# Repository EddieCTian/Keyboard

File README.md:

# Keyboard

Repository for .sch, .brd, and qmk configuration files for a keyboard I tried to desgin

## Version 1

Doesn't work due to a clock frequency mismatch between VCC (3.3V) and the required voltage for that clock (5V). As a result, it cannot connect to USB and also has layout issues. 

## Version 2

Fixed problems in version 1, but has yet to be checked or sent to a manufacturer to fabricate. 

Stopped working on this project since it got prohibitively expensive to purchase parts.

Maybe in the future it will become a working keyboard.

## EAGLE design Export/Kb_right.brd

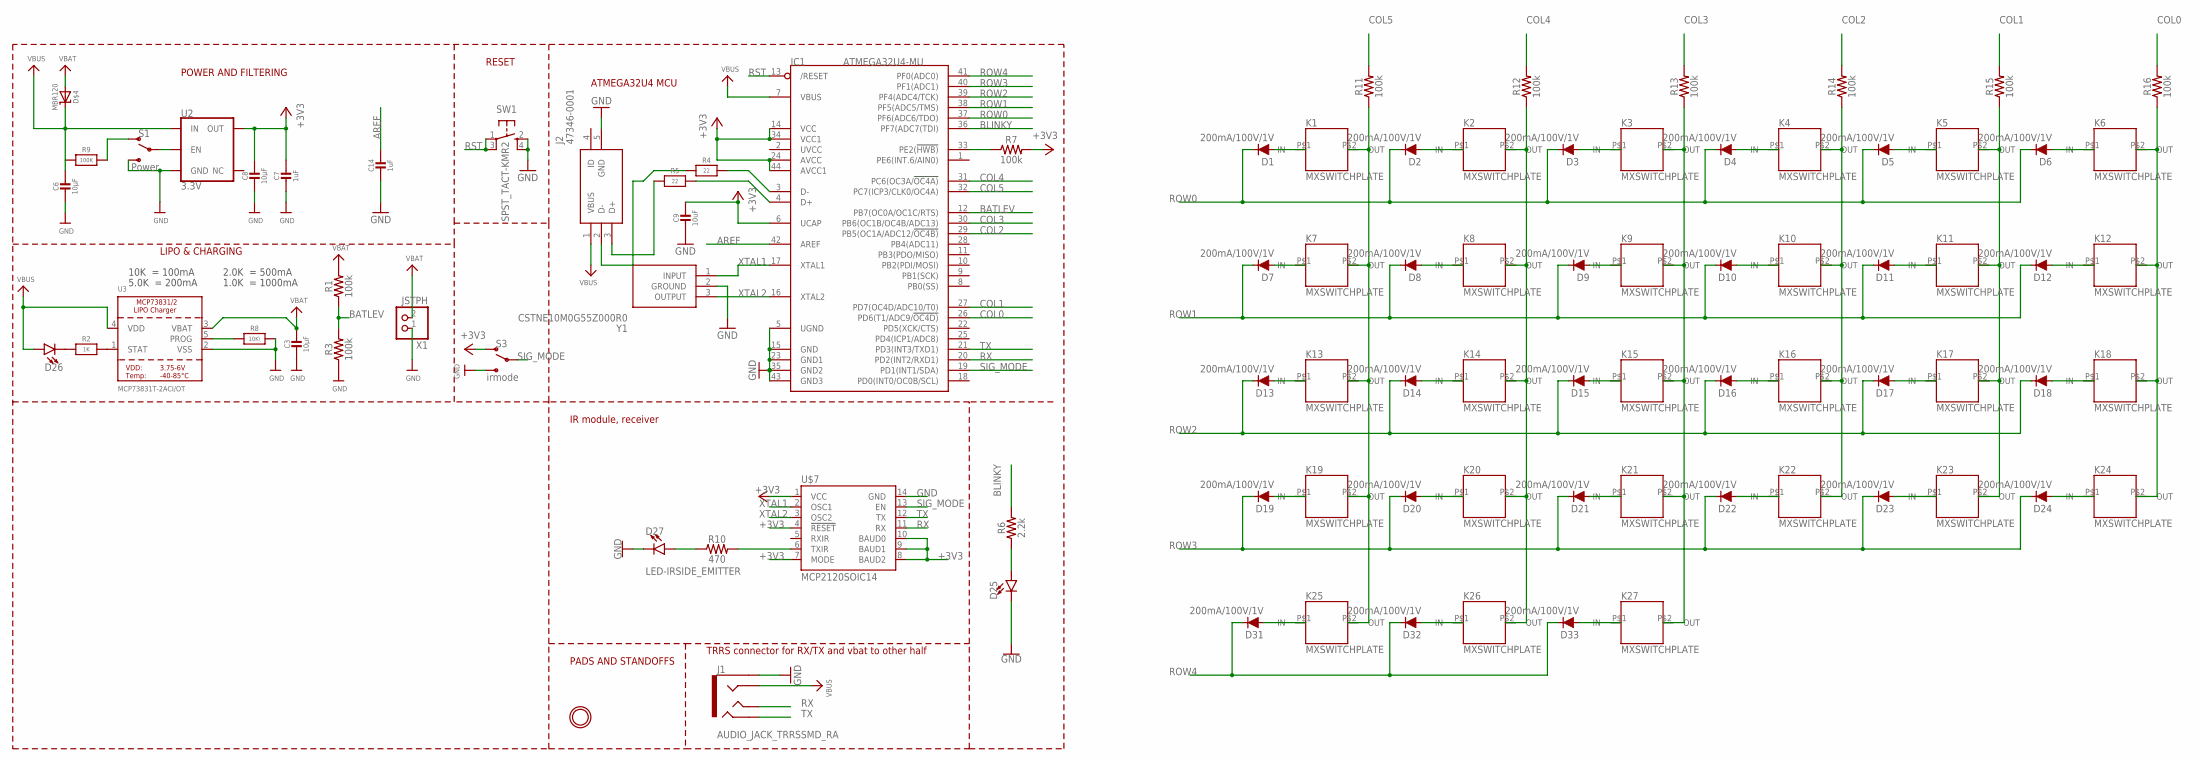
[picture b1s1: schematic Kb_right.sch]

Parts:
C3, C6, C8: 10µF; 0805-NO
C7, C14: 1uF; 0603-NO
C9: 10uF; _0805MP
D1, D2, D3, D4, D5, D6, D7, D8, D9, D10, D11, D12, D13, D14, D15, D16, D17, D18, D19, D20, D21, D22, D23, D24, D31, D32, D33: 200mA/100V/1V; DIODE-1N4148
D25, D26: LED-3MM-NO_SILK; LED_3MM-NS
D27: LED-IRSIDE_EMITTER; LTE-302
D$4: MBR120; SOD-123
IC1: ATMEGA32U4-MU; TQFN44_7MM
J1: AUDIO_JACK_TRRSSMD_RA; AUDIO_JACK_3.5MM_TRRS_SMD_RA
J2: 47346-0001
K1, K2, K3, K4, K5, K6, K7, K8, K9, K10, K11, K12, K13, K14, K15, K16, K17, K18, K19, K20, K21, K22, K23, K24, K25, K26, K27: MXSWITCHPLATE
R1, R3, R7, R11, R12, R13, R14, R15, R16: 100k; 0603
R2: 1K; 0603-NO
R4, R5: 22; 0603-NO
R6: 2.2k; 0603
R8: 10K\; 0603-NO
R9: 100K; 0603-NO
R10: 470; 0603
S1: Power; SWITCH_SPST_SMD_A
S3: irmode; SWITCH_SPST_SMD_A
SW1: SPST_TACT-KMR2; KMR2
U2: 3.3V; SOT23-5
U3: MCP73831T-2ACI/OT; SOT23-5
U$2: MOUNTINGHOLE2.5; MOUNTINGHOLE_2.5_PLATED
U$7: MCP2120SOIC14; SOIC127P600X175-14N
X1: JSTPH; JSTPH2
Y1: CSTNE10M0G55Z000R0

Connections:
+3V3: C7.1, C8.1, C9.1, IC1.6 (UCAP), IC1.14 (VCC), IC1.24 (AVCC), IC1.34 (VCC1), IC1.44 (AVCC1), R7.2, S3.1 (O), U2.5 (OUT), U$7.1 (VCC), U$7.4 (!RESET), U$7.7 (MODE), U$7.8 (BAUD2), U$7.9 (BAUD1), U$7.10 (BAUD0)
AREF: C14.1, IC1.42 (AREF)
BATLEV: IC1.12 (PB7(OC0A/OC1C/RTS)), R1.1, R3.2
BLINKY: IC1.36 (PF7(ADC7(TDI)), R6.2
COL0: IC1.26 (PD6(T1/ADC9/!OC4D)), R16.2
COL1: IC1.27 (PD7(OC4D/ADC10/T0)), R15.2
COL2: IC1.29 (PB5(OC1A/ADC12/!OC4B)), R14.2
COL3: IC1.30 (PB6(OC1B/OC4B/ADC13)), R13.2
COL4: IC1.31 (PC6(OC3A/!OC4A)), R12.2
COL5: IC1.32 (PC7(ICP3/CLK0/OC4A)), R11.2
D+: IC1.4 (D+), R5.2
D-: IC1.3 (D-), R4.2
GND: C3.2, C6.2, C7.2, C8.2, C9.2, C14.2, D25.K (C), D27.C, IC1.5 (UGND), IC1.15 (GND), IC1.23 (GND1), IC1.35 (GND2), IC1.43 (GND3), J1.EARTH, J2.5 (GND), R3.1, R8.2, S1.3 (S), S3.3 (S), SW1.2 (S), SW1.4 (S1), U2.2 (GND), U3.2 (VSS), U$7.14 (GND), X1.1, Y1.2 (GROUND)
unnamed: D26.K (C), R2.1
unnamed: D27.A, R10.1
unnamed: R2.2, U3.1 (STAT)
unnamed: R8.1, U3.5 (PROG)
unnamed: D25.A, R6.1
unnamed: IC1.33 (PE2(!HWB)), R7.1
unnamed: K1.P$2 (OUT), K7.P$2 (OUT), K13.P$2 (OUT), K19.P$2 (OUT), K25.P$2 (OUT), R11.1
unnamed: K2.P$2 (OUT), K8.P$2 (OUT), K14.P$2 (OUT), K20.P$2 (OUT), K26.P$2 (OUT), R12.1
unnamed: K3.P$2 (OUT), K9.P$2 (OUT), K15.P$2 (OUT), K21.P$2 (OUT), K27.P$2 (OUT), R13.1
unnamed: K4.P$2 (OUT), K10.P$2 (OUT), K16.P$2 (OUT), K22.P$2 (OUT), R14.1
unnamed: R9.2, S1.1 (O)
unnamed: S1.2, U2.3 (EN)
unnamed: K5.P$2 (OUT), K11.P$2 (OUT), K17.P$2 (OUT), K23.P$2 (OUT), R15.1
unnamed: K6.P$2 (OUT), K12.P$2 (OUT), K18.P$2 (OUT), K24.P$2 (OUT), R16.1
unnamed: J2.3 (D+), R5.1
unnamed: J2.2 (D-), R4.1
unnamed: R10.2, U$7.6 (TXIR)
unnamed: D1.A, K1.P$1 (IN)
unnamed: D2.A, K2.P$1 (IN)
unnamed: D3.A, K3.P$1 (IN)
unnamed: D4.A, K4.P$1 (IN)
unnamed: D5.A, K5.P$1 (IN)
unnamed: D6.A, K6.P$1 (IN)
unnamed: D12.A, K12.P$1 (IN)
unnamed: D11.A, K11.P$1 (IN)
unnamed: D10.A, K10.P$1 (IN)
unnamed: D9.A, K9.P$1 (IN)
unnamed: D8.A, K8.P$1 (IN)
unnamed: D7.A, K7.P$1 (IN)
unnamed: D13.A, K13.P$1 (IN)
unnamed: D14.A, K14.P$1 (IN)
unnamed: D15.A, K15.P$1 (IN)
unnamed: D16.A, K16.P$1 (IN)
unnamed: D17.A, K17.P$1 (IN)
unnamed: D18.A, K18.P$1 (IN)
unnamed: D24.A, K24.P$1 (IN)
unnamed: D23.A, K23.P$1 (IN)
unnamed: D22.A, K22.P$1 (IN)
unnamed: D21.A, K21.P$1 (IN)
unnamed: D20.A, K20.P$1 (IN)
unnamed: D19.A, K19.P$1 (IN)
unnamed: D33.A, K27.P$1 (IN)
unnamed: D32.A, K26.P$1 (IN)
unnamed: D31.A, K25.P$1 (IN)
ROW0: D1.C, D2.C, D3.C, D4.C, D5.C, D6.C, IC1.37 (PF6(ADC6/TDO))
ROW1: D7.C, D8.C, D9.C, D10.C, D11.C, D12.C, IC1.38 (PF5(ADC5/TMS))
ROW2: D13.C, D14.C, D15.C, D16.C, D17.C, D18.C, IC1.39 (PF4(ADC4/TCK))
ROW3: D19.C, D20.C, D21.C, D22.C, D23.C, D24.C, IC1.40 (PF1(ADC1))
ROW4: D31.C, D32.C, D33.C, IC1.41 (PF0(ADC0))
RST: IC1.13 (/RESET), SW1.1, SW1.3 (P1)
RX: IC1.20 (PD2(INT2/RXD1)), J1.TIP, U$7.11 (RX)
SIG_MODE: IC1.19 (PD1(INT1/SDA)), S3.2, U$7.13 (EN)
TX: IC1.21 (PD3(INT3/TXD1)), J1.RING2, U$7.12 (TX)
VBAT: C3.1, D$4.A, R1.2, U3.3 (VBAT), X1.2
VBUS: C6.1, D26.A, D$4.C, IC1.7 (VBUS), J1.RING1, J2.1 (VBUS), R9.1, U2.1 (IN), U3.4 (VDD)
XTAL1: IC1.17 (XTAL1), U$7.2 (OSC1), Y1.1 (INPUT)
XTAL2: IC1.16 (XTAL2), U$7.3 (OSC2), Y1.3 (OUTPUT)

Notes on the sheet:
POWER AND FILTERING
RESET
ATMEGA32U4 MCU
10K = 100mA
5.0K = 200mA
2.0K = 500mA
1.0K = 1000mA
LIPO & CHARGING
PADS AND STANDOFFS
TRRS connector for RX/TX and vbat to other half
IR module, receiver

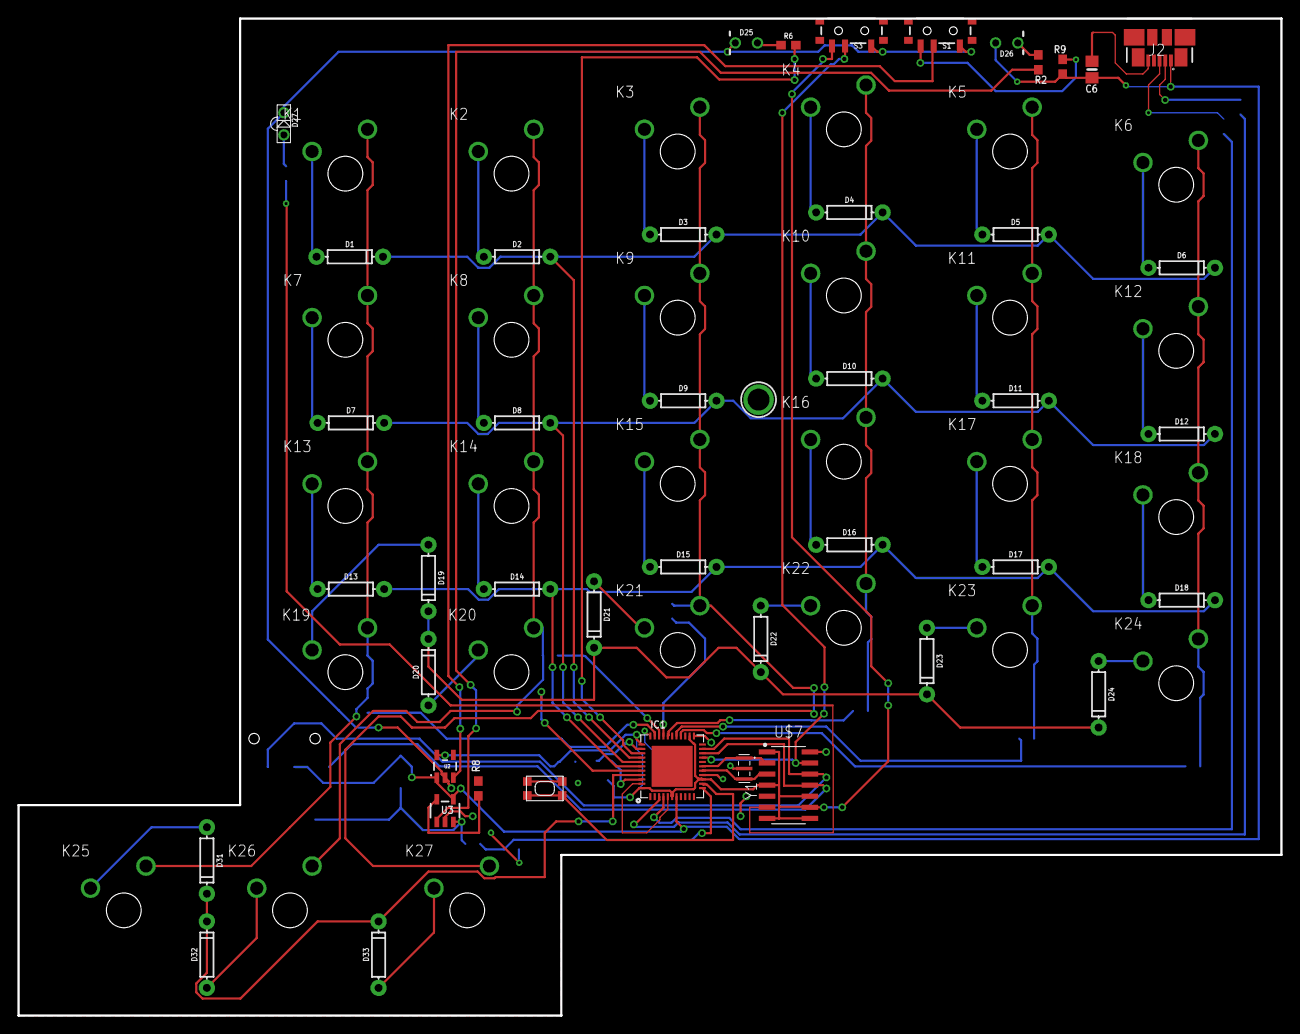
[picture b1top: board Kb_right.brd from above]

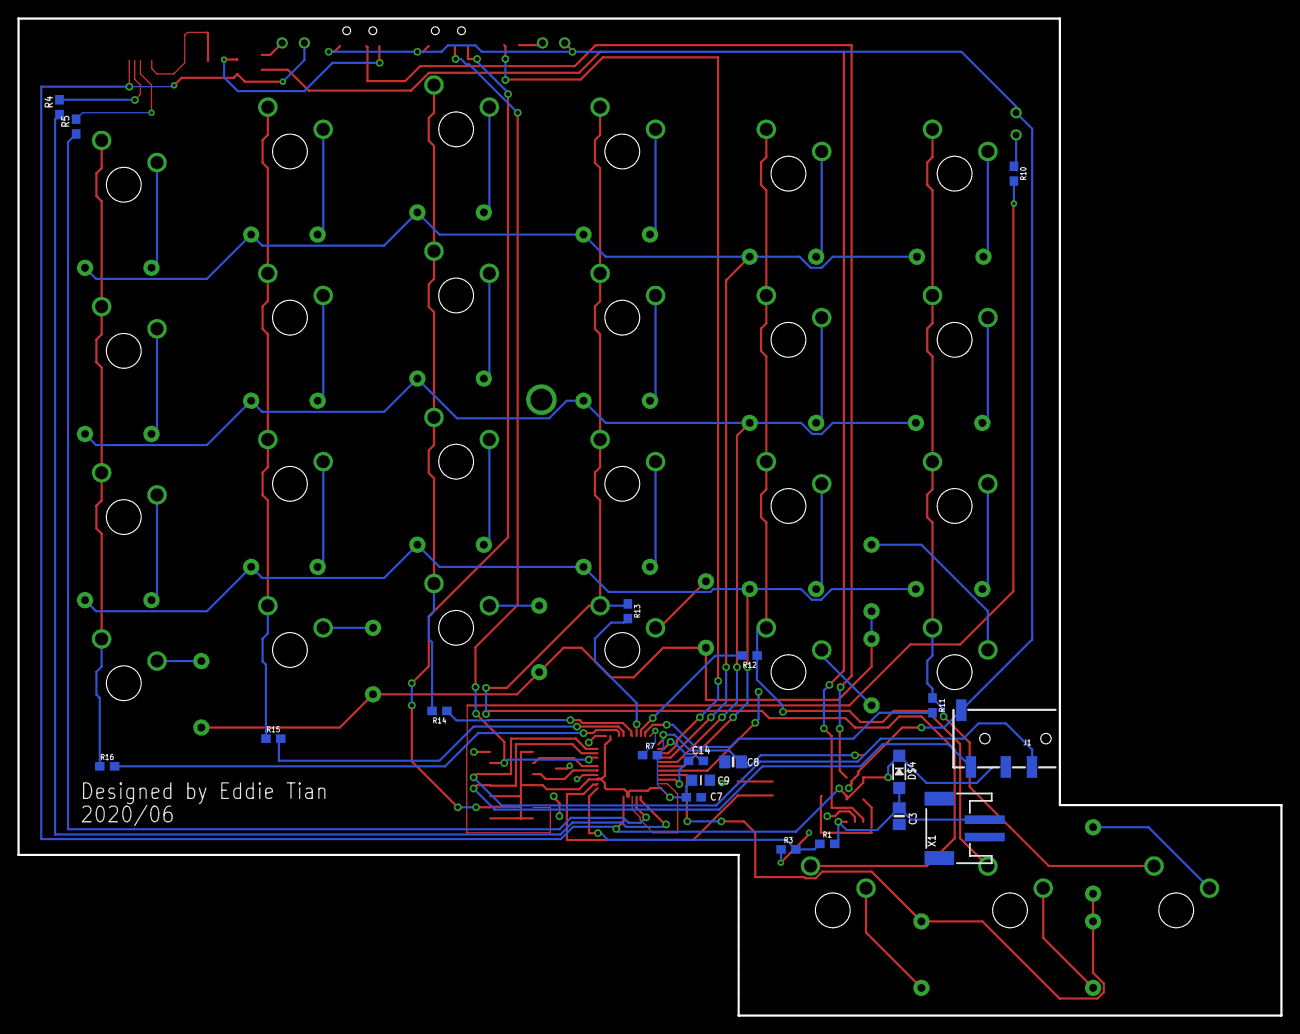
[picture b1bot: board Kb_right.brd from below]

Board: 2 copper layers, 144.8 x 114.3 mm, 92 parts (20 on the bottom side), 70 nets.

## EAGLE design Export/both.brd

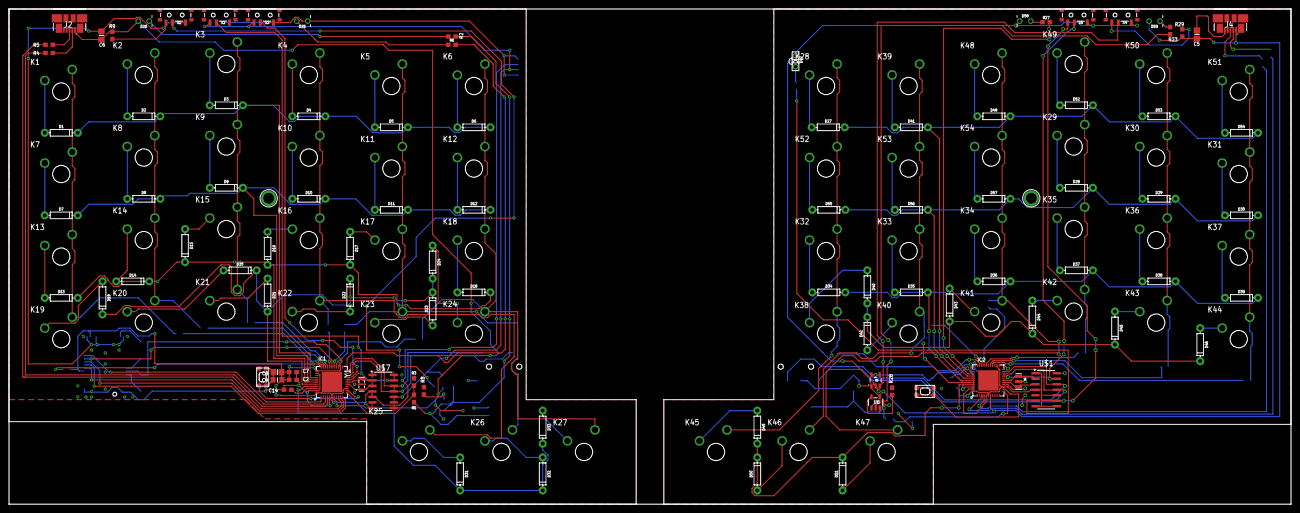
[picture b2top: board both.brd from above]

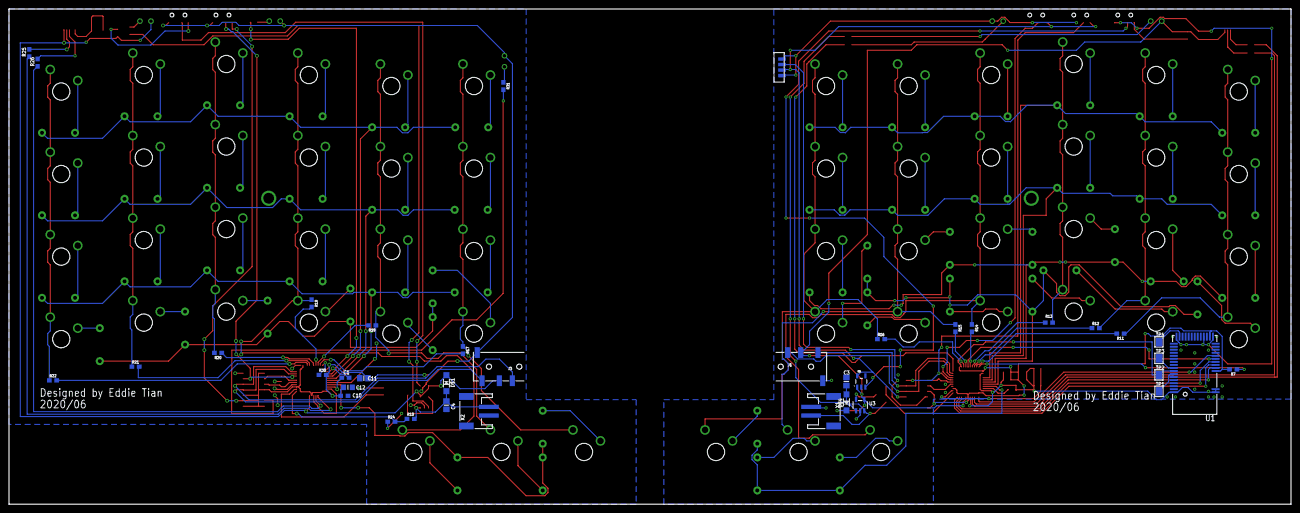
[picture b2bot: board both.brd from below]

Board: 2 copper layers, 295.9 x 114.3 mm, 190 parts (39 on the bottom side), 149 nets.

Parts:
C1, C2, C7, C10, C14: 1uF; 0603-NO
C3, C4, C5, C6, C8, C11: 10µF; 0805-NO
C9, C12: 10uF; _0805MP
D1, D2, D3, D4, D5, D6, D7, D8, D9, D10, D11, D12, D13, D14, D15, D16, D17, D18, D19, D20, D21, D22, D23, D24, D27, D28, D29, D30, D31, D32, D33, D34, D35, D36, D37, D38, D39, D40, D41, D42, D43, D44, D45, D46, D48, D49, D50, D51, D52, D53, D54, D55, D56, D57: 200mA/100V/1V; DIODE-1N4148
D25, D26, D58, D59: LED_3MM-NS
D47: LED-IRSIDE_EMITTER; LTE-302
D$1, D$4: MBR120; SOD-123
IC1, IC2: ATMEGA32U4-MU; TQFN44_7MM
J1, J3: AUDIO_JACK_TRRSSMD_RA; AUDIO_JACK_3.5MM_TRRS_SMD_RA
J2, J4: 47346-0001
K1, K2, K3, K4, K5, K6, K7, K8, K9, K10, K11, K12, K13, K14, K15, K16, K17, K18, K19, K20, K21, K22, K23, K24, K25, K26, K27, K28, K29, K30, K31, K32, K33, K34, K35, K36, K37, K38, K39, K40, K41, K42, K43, K44, K45, K46, K47, K48, K49, K50, K51, K52, K53, K54: MXSWITCHPLATE
R1, R3, R7, R10, R11, R12, R13, R14, R15, R16, R17, R18, R19, R20, R21, R22, R24, R30: 100k; 0603
R2, R23: 1K; 0603-NO
R4, R5, R25, R26: 22; 0603-NO
R6, R27: 2.2k; 0603
R8, R28: 10K\; 0603-NO
R9, R29: 100K; 0603-NO
R31: 470; 0603
S1, S4: Power; SWITCH_SPST_SMD_A
S2: bt_mode; SWITCH_SPST_SMD_A
S3, S5: irmode; SWITCH_SPST_SMD_A
SW1, SW2: SPST_TACT-KMR2; KMR2
TP1: SWCLK; PAD-1.5X2.0
TP2, TP3: SWDIO; PAD-1.5X2.0
TP4: DFU; PAD-1.5X2.0
U1: MBT40; BLE_MODULE_RAYTAC_MDBT40
U2, U5: 3.3V; SOT23-5
U3: MCP73831; SOT23-5
U4: TSOP75456
U6: MCP73831T-2ACI/OT; SOT23-5
U$1: MCP2120SOIC14; SOIC127P600X175-14N
U$2, U$11: MOUNTINGHOLE2.5; MOUNTINGHOLE_2.5_PLATED
U$7: MCP2120; SOIC127P600X175-14N
X1, X2: JSTPH; JSTPH2
Y1: CSTNE10M0G55Z000R0
Y2: 8MHz; RESONATOR-SMD

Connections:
4_SWDIO/RST: IC1.25, TP2.P$1, U1.35
7_BLE_IRQ: IC1.1, U1.8
8_BLE_CS: IC1.28, U1.7
+3V1: C10.1, C11.1, C12.1, IC2.6, IC2.14, IC2.24, IC2.34, IC2.44, R30.2, S5.1, U5.5, U$1.1, U$1.4, U$1.7, U$1.8, U$1.9, U$1.10
+3V3: C2.1, C7.1, C8.1, C9.1, IC1.6, IC1.14, IC1.24, IC1.34, IC1.44, R7.2, S2.1, S3.1, U1.3, U1.14, U2.5, U4.VCC, U$7.1, U$7.4, U$7.7, U$7.8, U$7.9, U$7.10
AREF: C14.1, IC1.42
AREF1: C1.1, IC2.42
BATLEV: IC1.12, R1.1, R3.2
BATLEV1: IC2.12, R10.1, R24.2
BLINKY: IC1.22, R6.2
BLINKY1: IC2.36, R27.2
COL0: IC1.26, R16.2
COL1: IC1.27, R15.2
COL2: IC1.29, R14.2
COL3: IC1.30, R13.2
COL4: IC1.31, R12.2
COL5: IC1.32, R11.2
COL6: IC2.26, R22.2
COL7: IC2.27, R21.2
COL8: IC2.29, R20.2
COL9: IC2.30, R19.2
COL10: IC2.31, R18.2
COL11: IC2.32, R17.2
D+: IC1.4, R5.2
D+1: IC2.4, R26.2
D-: IC1.3, R4.2
D-1: IC2.3, R25.2
DFU: TP4.P$1, U1.24
FCTRYRST: TP3.P$1, U1.34
GND: C2.2, C3.2, C6.2, C7.2, C8.2, C9.2, C14.2, D25.K, IC1.5, IC1.15, IC1.23, IC1.35, IC1.43, J1.EARTH, J2.5, R3.1, R8.2, S1.3, S2.3, S3.3, SW1.2, SW1.4, U1.1, U1.2, U1.13, U1.16, U1.25, U1.42, U2.2, U3.2, U4.$GND, U4.GND, U$7.14, X1.1, Y1.2
GND1: C1.2, C4.2, C5.2, C10.2, C11.2, C12.2, D47.C, D58.K, IC2.5, IC2.15, IC2.23, IC2.35, IC2.43, J3.EARTH, J4.5, R24.1, R28.2, S4.3, S5.3, SW2.2, SW2.4, U5.2, U6.2, U$1.14, X2.1, Y2.2
MISO: IC1.11, U1.5
MODE: IC1.18, S2.2, U$7.13
MOSI: IC1.10, U1.6
unnamed: D26.K, R2.1
unnamed: IC1.33, R7.1
unnamed: R2.2, U3.1
unnamed: R8.1, U3.5
unnamed: D25.A, R6.1
unnamed: J2.3, R5.1
unnamed: K1.P$2, K7.P$2, K13.P$2, K19.P$2, R11.1
unnamed: K2.P$2, K8.P$2, K14.P$2, K20.P$2, R12.1
unnamed: K3.P$2, K9.P$2, K15.P$2, K21.P$2, R13.1
unnamed: K4.P$2, K10.P$2, K16.P$2, K22.P$2, K25.P$2, R14.1
unnamed: R9.2, S1.1
unnamed: S1.2, U2.3
unnamed: K5.P$2, K11.P$2, K17.P$2, K23.P$2, K26.P$2, R15.1
unnamed: K6.P$2, K12.P$2, K18.P$2, K24.P$2, K27.P$2, R16.1
unnamed: J4.2, R25.1
unnamed: J2.2, R4.1
unnamed: R23.2, U6.1
unnamed: R28.1, U6.5
unnamed: K28.P$2, K32.P$2, K38.P$2, K45.P$2, K52.P$2, R17.1
unnamed: K33.P$2, K39.P$2, K40.P$2, K46.P$2, K53.P$2, R18.1
unnamed: K34.P$2, K41.P$2, K47.P$2, K48.P$2, K54.P$2, R19.1
unnamed: K29.P$2, K35.P$2, K42.P$2, K49.P$2, R20.1
unnamed: D1.A, K1.P$1
unnamed: D2.A, K2.P$1
unnamed: D3.A, K3.P$1
unnamed: D4.A, K4.P$1
unnamed: D5.A, K5.P$1
unnamed: D6.A, K6.P$1
unnamed: D12.A, K12.P$1
unnamed: D11.A, K11.P$1
unnamed: D10.A, K10.P$1
unnamed: D9.A, K9.P$1
unnamed: D8.A, K8.P$1
unnamed: D7.A, K7.P$1
unnamed: D13.A, K13.P$1
unnamed: D14.A, K14.P$1
unnamed: D15.A, K15.P$1
unnamed: D16.A, K16.P$1
unnamed: D17.A, K17.P$1
unnamed: D18.A, K18.P$1
unnamed: D24.A, K24.P$1
unnamed: D23.A, K23.P$1
unnamed: D22.A, K22.P$1
unnamed: D21.A, K21.P$1
unnamed: D20.A, K20.P$1
unnamed: D19.A, K19.P$1
unnamed: K30.P$2, K36.P$2, K43.P$2, K50.P$2, R21.1
unnamed: K31.P$2, K37.P$2, K44.P$2, K51.P$2, R22.1
unnamed: D27.A, K28.P$1
unnamed: D41.A, K39.P$1
unnamed: D48.A, K48.P$1
unnamed: D52.A, K49.P$1
unnamed: D33.A, K27.P$1
unnamed: D32.A, K26.P$1
unnamed: D31.A, K25.P$1
unnamed: D53.A, K50.P$1
unnamed: D54.A, K51.P$1
unnamed: D30.A, K31.P$1
unnamed: D29.A, K30.P$1
unnamed: D28.A, K29.P$1
unnamed: D57.A, K54.P$1
unnamed: D56.A, K53.P$1
unnamed: D55.A, K52.P$1
unnamed: U4.OUT, U$7.5
unnamed: D34.A, K32.P$1
unnamed: D35.A, K33.P$1
unnamed: D36.A, K34.P$1
unnamed: D37.A, K35.P$1
unnamed: D38.A, K36.P$1
unnamed: D39.A, K37.P$1
unnamed: D46.A, K44.P$1
unnamed: D45.A, K43.P$1
unnamed: D44.A, K42.P$1
unnamed: D43.A, K41.P$1
unnamed: D42.A, K40.P$1
unnamed: D40.A, K38.P$1
unnamed: D51.A, K47.P$1
unnamed: D50.A, K46.P$1
unnamed: D49.A, K45.P$1
unnamed: S4.2, U5.3
unnamed: R29.2, S4.1
unnamed: D58.A, R27.1
unnamed: D59.K, R23.1
unnamed: IC2.33, R30.1
unnamed: D47.A, R31.1
unnamed: R31.2, U$1.6
unnamed: J4.3, R26.1
ROW0: D1.C, D2.C, D3.C, D4.C, D5.C, D6.C, IC1.37
ROW1: D7.C, D8.C, D9.C, D10.C, D11.C, D12.C, IC1.38
ROW2: D13.C, D14.C, D15.C, D16.C, D17.C, D18.C, IC1.39
ROW3: D19.C, D20.C, D21.C, D22.C, D23.C, D24.C, IC1.40
ROW4: D31.C, D32.C, D33.C, IC1.41
ROW5: D27.C, D41.C, D48.C, D52.C, D53.C, D54.C, IC2.37
ROW6: D40.C, D42.C, D43.C, D44.C, D45.C, D46.C, IC2.40
ROW7: D34.C, D35.C, D36.C, D37.C, D38.C, D39.C, IC2.39
ROW8: D28.C, D29.C, D30.C, D55.C, D56.C, D57.C, IC2.38
ROW9: D49.C, D50.C, D51.C, IC2.41
RST: IC1.13, SW1.1, SW1.3
RST1: IC2.13, SW2.1, SW2.3
RX: IC1.20, J1.RING2, U$7.11
RX1: IC2.20, J3.TIP, U$1.11
SCK: IC1.9, U1.4
SIG_MODE: IC1.19, S3.2
SIG_MODE1: IC2.19, S5.2, U$1.13
SWCLK: TP1.P$1, U1.36
TX: IC1.21, J1.TIP, U$7.12
TX1: IC2.21, J3.RING2, U$1.12
VBAT: C3.1, D$4.A, R1.2, U3.3, X1.2
VBAT1: C4.1, D$1.A, R10.2, U6.3, X2.2
VBUS: C6.1, D26.A, D$4.C, IC1.7, J1.RING1, J2.1, R9.1, U2.1, U3.4
VBUS1: C5.1, D59.A, D$1.C, IC2.7, J3.RING1, J4.1, R29.1, U5.1, U6.4
XTAL1: IC1.17, U$7.2, Y1.3
XTAL2: IC1.16, U$7.3, Y1.1
XTAL3: IC2.16, U$1.3, Y2.3
XTAL4: IC2.17, U$1.2, Y2.1

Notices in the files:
parts and their libraries:
microbuilder: This work is placed in the public domain, and may be freely used for commercial and non-commercial work with the following conditions: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
SparkFun-DiscreteSemi: Licensing: Creative Commons ShareAlike 4.0 International - https://creativecommons.org/licenses/by-sa/4.0
